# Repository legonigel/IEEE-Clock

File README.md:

# IEEE-Clock
The clock project for the IEEE
You can edit this using EAGLE CAD

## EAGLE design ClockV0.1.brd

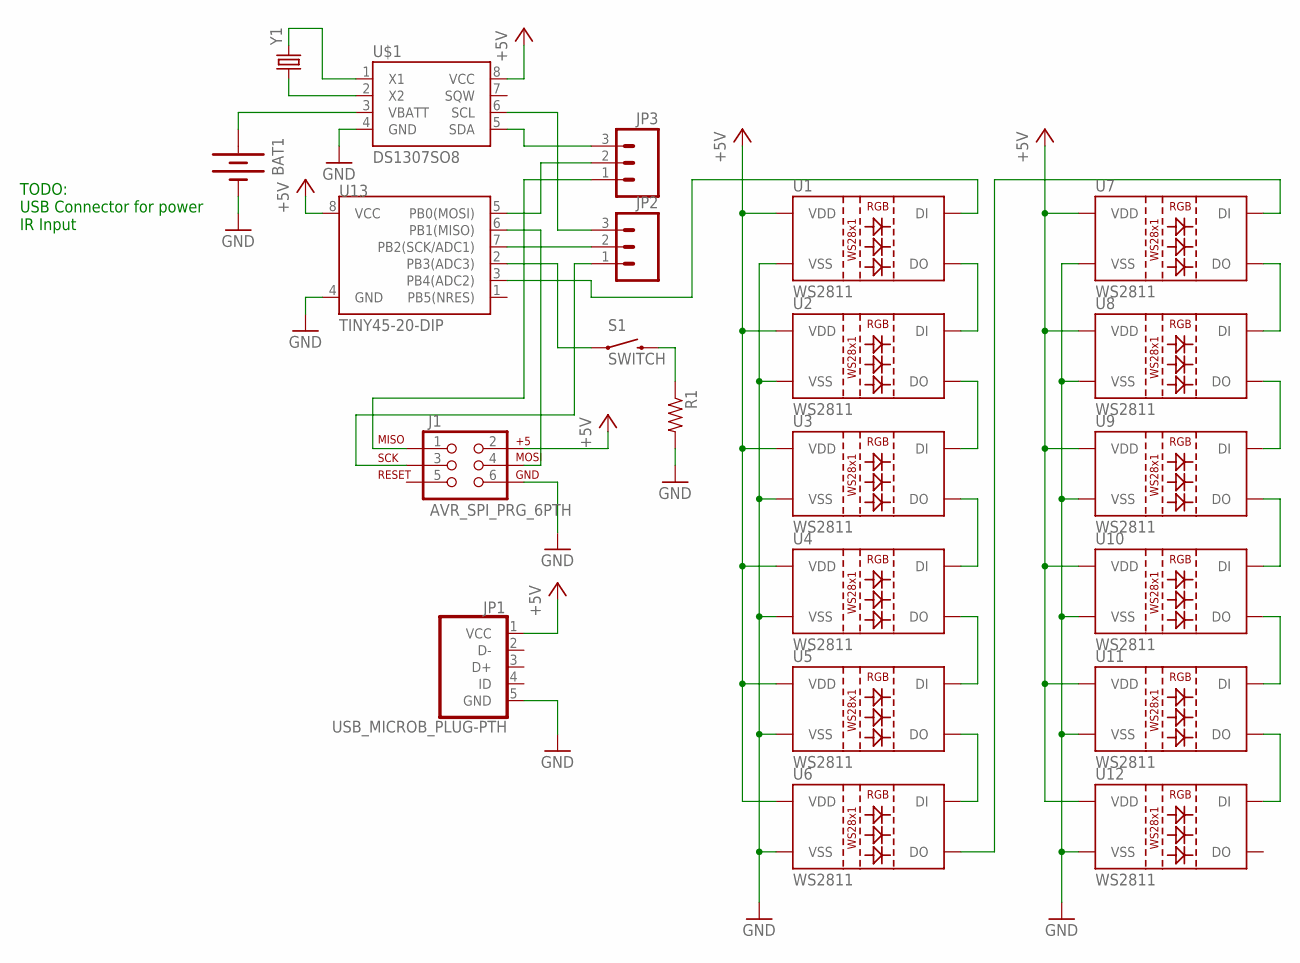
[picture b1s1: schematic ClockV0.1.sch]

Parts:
BAT1: BATTERY12PTH; BATTCON_12MM_PTH
J1: AVR_SPI_PRG_6PTH; 2X3
JP1: USB_MICROB_PLUG-PTH; MICRO-B-RA-TH
JP2, JP3: M03PTH; 1X03
R1: RESISTORPTH-1/2W; AXIAL-0.5
S1: SWITCH; TACTILE-PTH
U1, U2, U3, U4, U5, U6, U7, U8, U9, U10, U11, U12: WS2811; LED-TRICOLOR-5050-IC
U13: TINY45-20-DIP; DIP08
U$1: DS1307SO8; SO08
Y1: CRYSTAL32-SMD; CRYSTAL-32KHZ-SMD

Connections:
+5V: J1.2, JP1.1 (VCC), U1.3 (VDD), U1.5 (VDD), U2.3 (VDD), U2.5 (VDD), U3.3 (VDD), U3.5 (VDD), U4.3 (VDD), U4.5 (VDD), U5.3 (VDD), U5.5 (VDD), U6.3 (VDD), U6.5 (VDD), U7.3 (VDD), U7.5 (VDD), U8.3 (VDD), U8.5 (VDD), U9.3 (VDD), U9.5 (VDD), U10.3 (VDD), U10.5 (VDD), U11.3 (VDD), U11.5 (VDD), U12.3 (VDD), U12.5 (VDD), U13.8 (VCC), U$1.8 (VCC)
GND: BAT1.GND (-), J1.6, JP1.5 (GND), R1.P$2 (2), U1.6 (VSS), U2.6 (VSS), U3.6 (VSS), U4.6 (VSS), U5.6 (VSS), U6.6 (VSS), U7.6 (VSS), U8.6 (VSS), U9.6 (VSS), U10.6 (VSS), U11.6 (VSS), U12.6 (VSS), U13.4 (GND), U$1.4 (GND)
unnamed: U7.1 (DO), U8.2 (DI)
unnamed: U8.1 (DO), U9.2 (DI)
unnamed: U1.1 (DO), U2.2 (DI)
unnamed: U2.1 (DO), U3.2 (DI)
unnamed: U3.1 (DO), U4.2 (DI)
unnamed: U4.1 (DO), U5.2 (DI)
unnamed: U5.1 (DO), U6.2 (DI)
unnamed: U6.1 (DO), U7.2 (DI)
unnamed: U9.1 (DO), U10.2 (DI)
unnamed: U10.1 (DO), U11.2 (DI)
unnamed: U11.1 (DO), U12.2 (DI)
unnamed: J1.1, JP3.1
unnamed: J1.4, U13.6 (PB1(MISO))
unnamed: U1.2 (DI), U13.3 (PB4(ADC2))
unnamed: J1.3, JP2.1
unnamed: BAT1.VCC@1 (+), U$1.3 (VBATT)
unnamed: U$1.2 (X2), Y1.X1 (1)
unnamed: U$1.1 (X1), Y1.X2 (2)
unnamed: JP2.3, U$1.6 (SCL)
unnamed: JP2.2, U13.7 (PB2(SCK/ADC1))
unnamed: JP3.2, U13.5 (PB0(MOSI))
unnamed: JP3.3, U$1.5 (SDA)
unnamed: S1.1, U13.2 (PB3(ADC3))
unnamed: R1.P$1 (1), S1.3 (2)

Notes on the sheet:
TODO: USB Connector for power IR Input

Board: 2 copper layers, 22 parts (3 on the bottom side), 26 nets, no tracks yet.

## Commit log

2015-04-07 Initial commit Board and Schmatic

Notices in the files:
parts and their libraries:
SparkFun-LED: Licensing: CC v3.0 Share-Alike You are welcome to use this library for commercial purposes.
